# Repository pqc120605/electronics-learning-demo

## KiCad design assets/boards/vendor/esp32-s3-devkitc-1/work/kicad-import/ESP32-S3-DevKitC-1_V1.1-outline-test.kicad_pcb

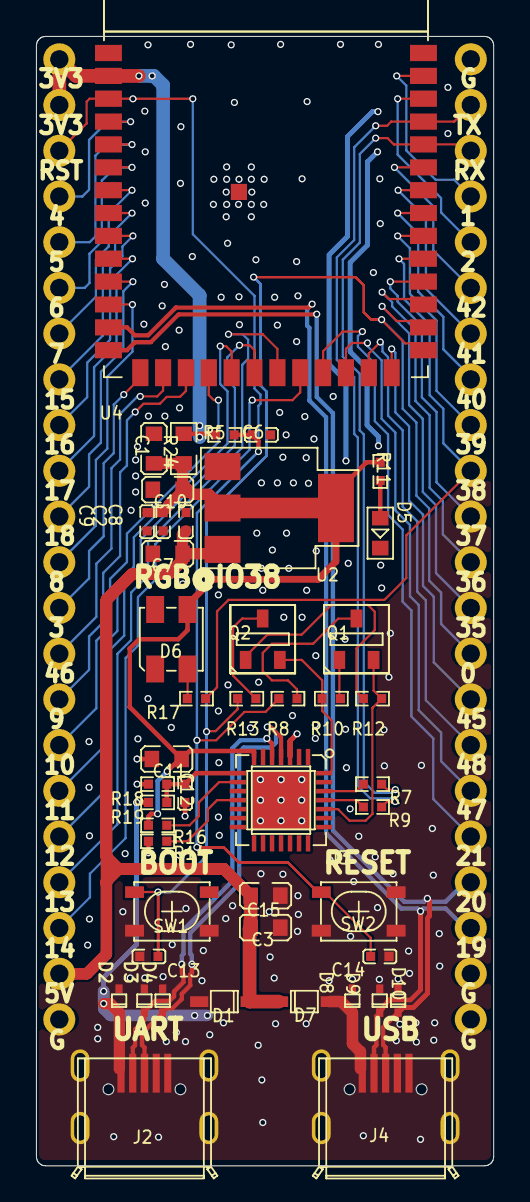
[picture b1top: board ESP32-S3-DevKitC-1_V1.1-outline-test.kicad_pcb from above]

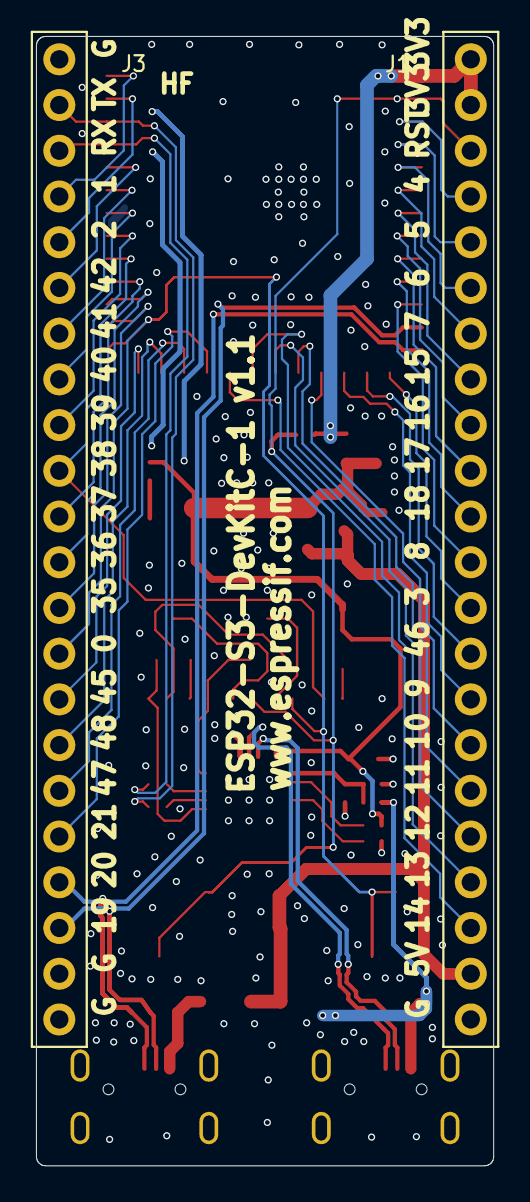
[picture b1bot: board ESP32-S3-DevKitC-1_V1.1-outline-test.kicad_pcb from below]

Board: 2 copper layers, 25.4 x 62.7 mm, 48 parts (2 on the bottom side), 58 nets.

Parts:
C1, C3, C7, C10, C11, C15: C0603
C2, C6, C8, C9, C12, C13, C14: C0402
D1, D7: SOD123
D2, D3, D4, D8, D9, D10: SOD523
D5: LED0603
D6: LED3535B
J1, J3: CON22X1_2P54_OBLATE
J2, J4: USB_5P_MICRO_F_ML
Q1, Q2: SOT23-3
R5, R7, R8, R9, R10, R11, R12, R13, R14, R16, R17, R18, R19: R0402
R24: R0603
SW1, SW2: SW4-4P2X3P2X2P5-SMT
U2: SOT223
U3: QFN28_0P5_5
U4: ESP32-S3-WROOM_NEW

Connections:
CHIP_PU: C6.1, C14.2, J1.3, R5.1, R8.2, SW2.3, U4.3
D+: D4.2, J2.3, U3.4
D-: D3.2, J2.2, U3.5
DTR: Q2.2, R10.1, U3.28
ESP_3V3: J1.1, J1.2, R5.2, R24.2, U4.2
GND: C1.2, C2.2, C3.2, C6.2, C7.2, C8.2, C9.2, C10.2, C11.2, C12.2, C13.1, C14.1, C15.2, D2.1, D3.1, D4.1, D5.2, D6.1, D8.1, D9.1, D10.1, J1.22, J2.5, J2.6, J2.7, J2.8, J2.9, J3.1, J3.21, J3.22, J4.5, J4.6, J4.7, J4.8, J4.9, R14.2, R18.2, SW1.1, SW2.1, U2.1, U3.3, U3.29, U4.1, U4.40, U4.41
GPIO0: C13.2, J3.14, R13.2, SW1.3, U4.27
GPIO1: J3.4, U4.39
GPIO2: J3.5, U4.38
GPIO3: J1.13, U4.15
GPIO4: J1.4, U4.4
GPIO5: J1.5, U4.5
GPIO6: J1.6, U4.6
GPIO7: J1.7, U4.7
GPIO8: J1.12, U4.12
GPIO9: J1.15, U4.17
GPIO10: J1.16, U4.18
GPIO11: J1.17, U4.19
GPIO12: J1.18, U4.20
GPIO13: J1.19, U4.21
GPIO14: J1.20, U4.22
GPIO15: J1.8, U4.8
GPIO16: J1.9, U4.9
GPIO17: J1.10, U4.10
GPIO18: J1.11, U4.11
GPIO19: D9.2, J3.20, J4.2, U4.13
GPIO20: D10.2, J3.19, J4.3, U4.14
GPIO21: J3.18, U4.23
GPIO35: J3.13, U4.28
GPIO36: J3.12, U4.29
GPIO37: J3.11, U4.30
GPIO38: J3.10, R17.1, U4.31
GPIO39: J3.9, U4.32
GPIO40: J3.8, U4.33
GPIO41: J3.7, U4.34
GPIO42: J3.6, U4.35
GPIO45: J3.15, U4.26
GPIO46: J1.14, U4.16
GPIO47: J3.17, U4.24
GPIO48: J3.16, U4.25
N17688270: C12.1, R18.1, R19.2, U3.8
N17688616: R16.1, U3.9
N17688663: R14.1, U3.11
N17689011: R7.1, U3.26
N17689016: R9.1, U3.25
N17689859: Q1.1, R10.2
N17689862: Q2.1, R12.2
N17689962: Q2.3, R13.1
N17689967: Q1.3, R8.1
N17692194: D5.1, R11.2
RGB_CTRL: D6.2, R17.2
RTS: Q1.2, R12.1, U3.24
U0RXD: J3.3, R7.2, U4.36
U0TXD: J3.2, R9.2, U4.37
VBUS: D1.1, D2.2, J2.1, R19.1
VBUSB: D7.1, D8.2, J4.1
VCC_3V3: C1.1, C2.1, C9.1, C10.1, C11.1, D6.3, R11.1, R16.2, R24.1, U2.2, U2.4, U3.6, U3.7
VCC_5V: C3.1, C7.1, C8.1, C15.1, D1.2, D7.2, J1.21, U2.3

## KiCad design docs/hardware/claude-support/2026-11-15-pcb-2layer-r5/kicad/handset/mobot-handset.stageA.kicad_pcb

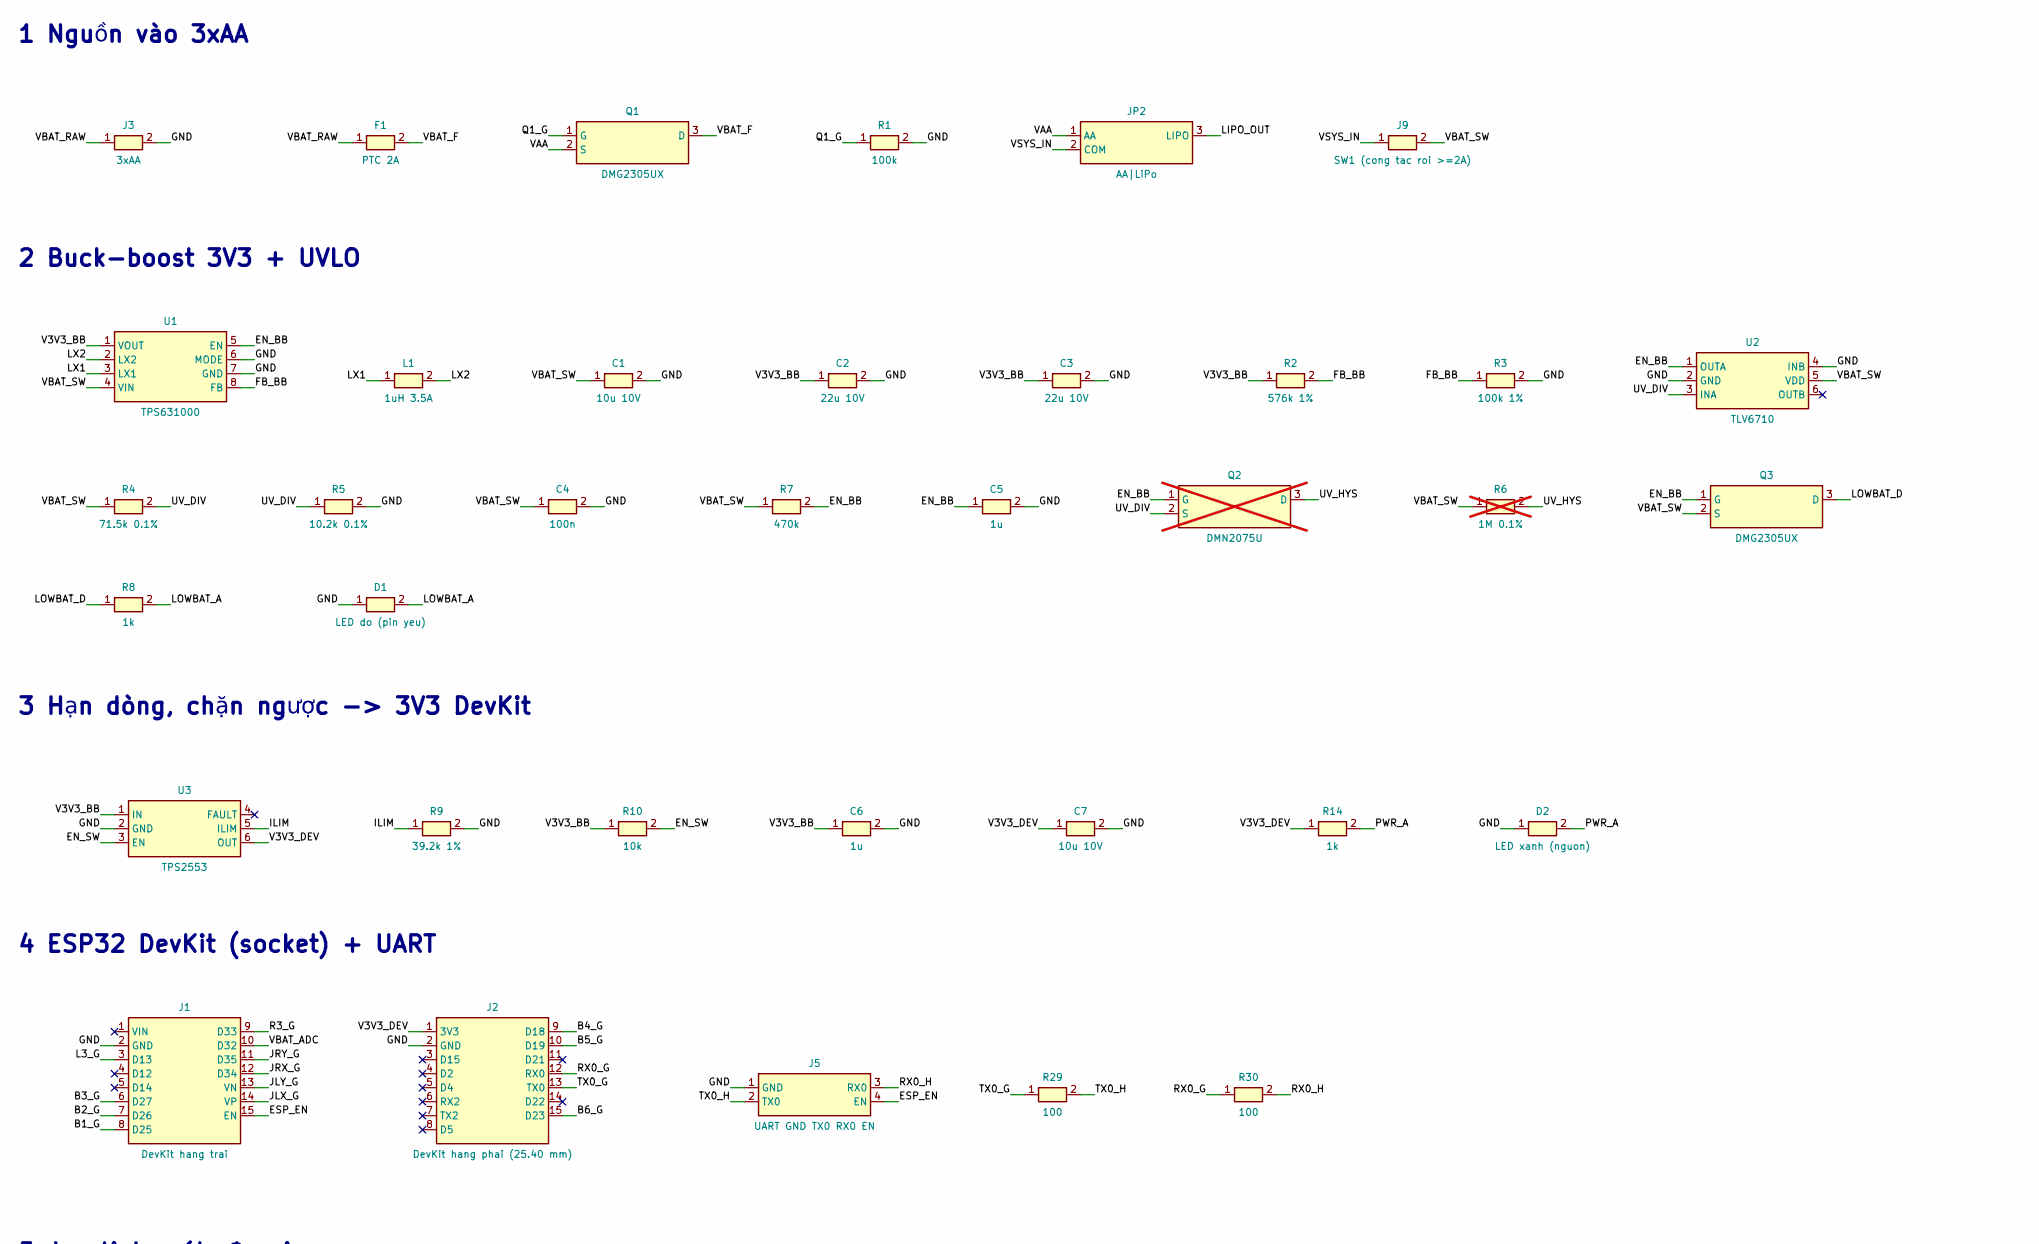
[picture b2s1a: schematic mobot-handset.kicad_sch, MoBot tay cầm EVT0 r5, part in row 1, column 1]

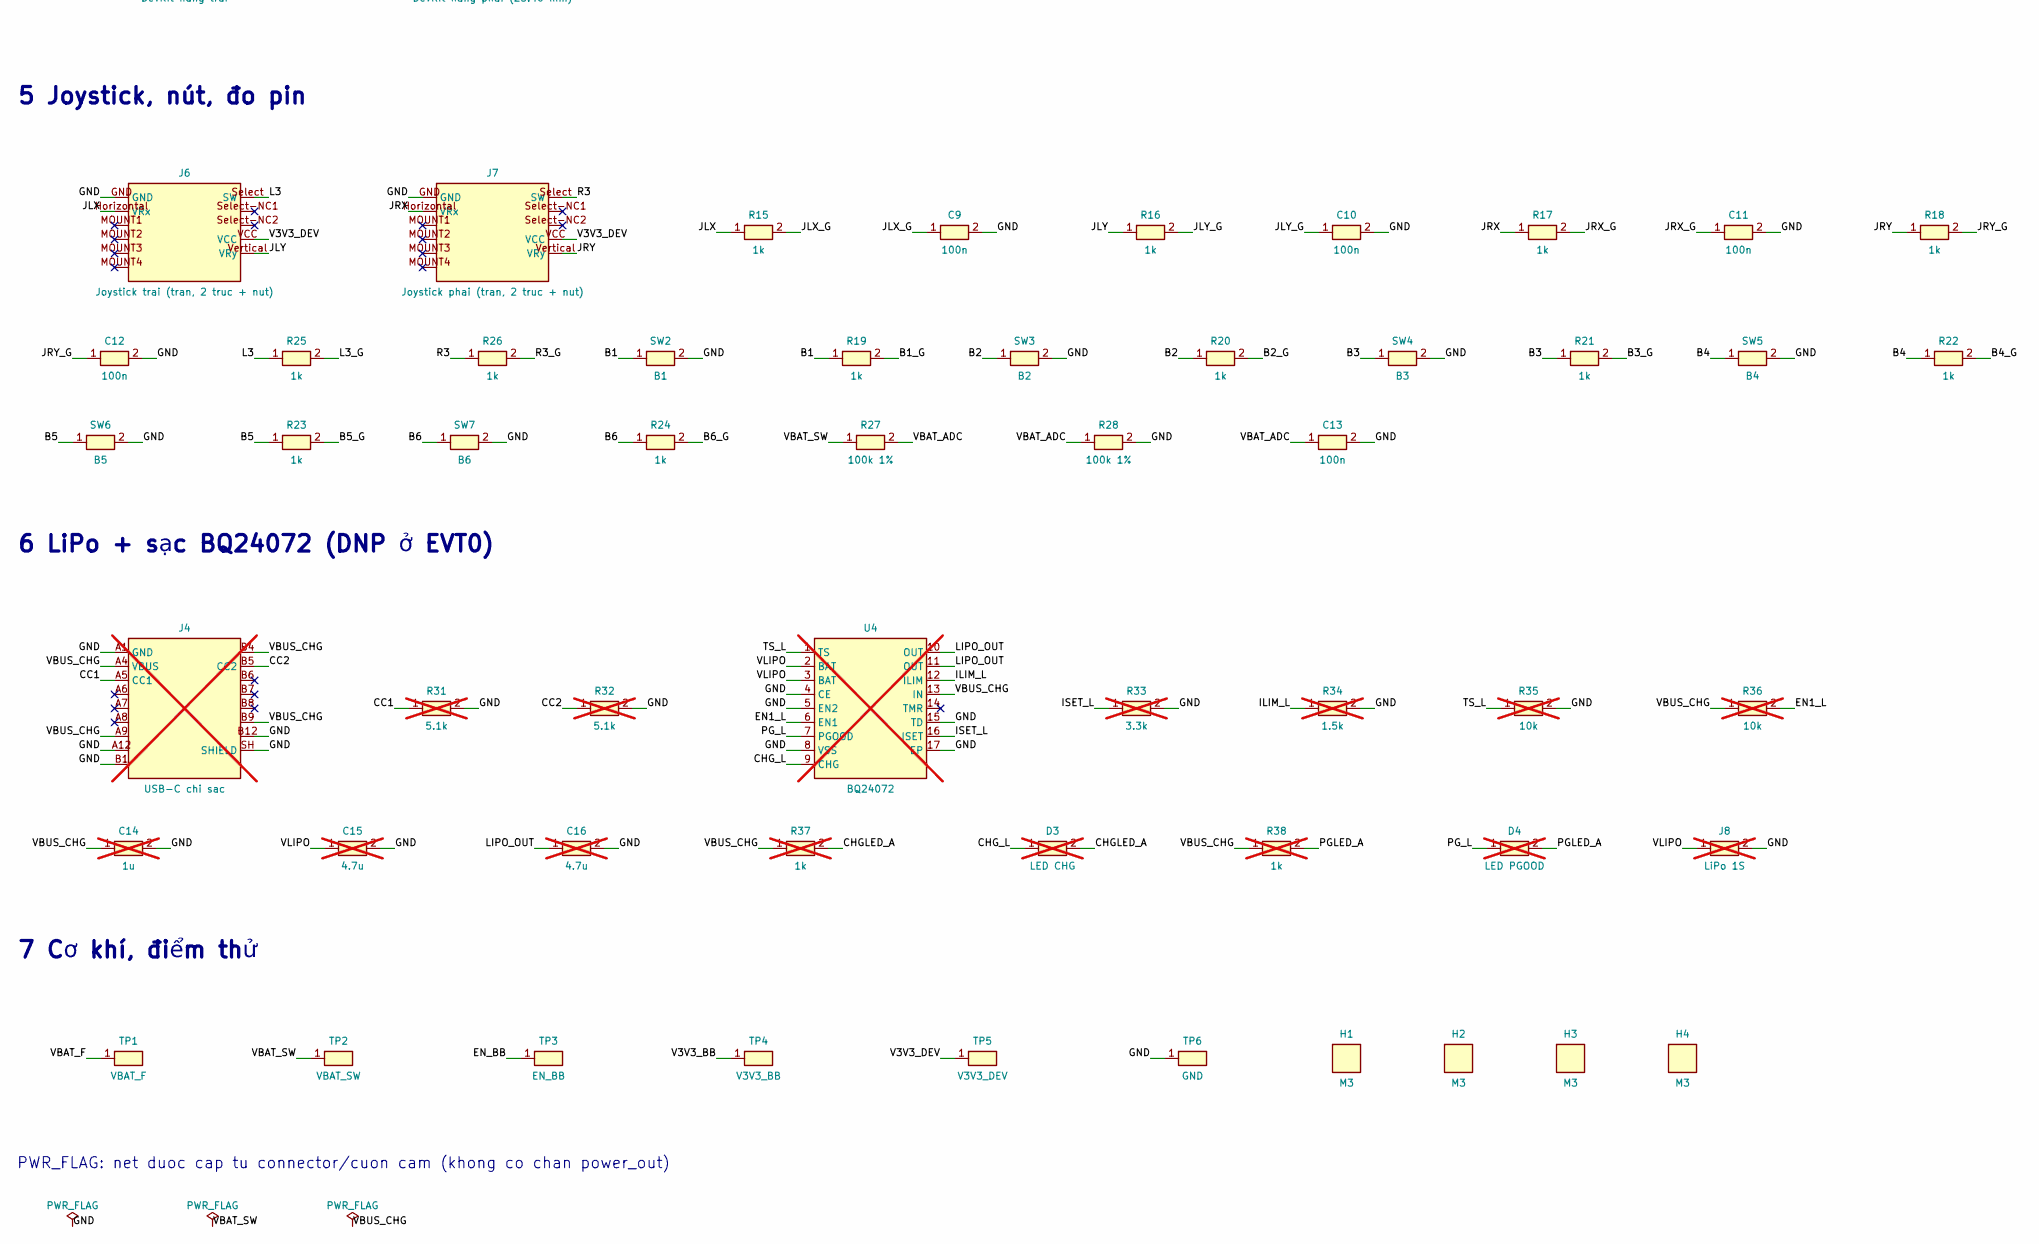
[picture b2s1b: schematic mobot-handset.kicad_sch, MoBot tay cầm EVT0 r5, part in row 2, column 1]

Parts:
C1, C7: 10u 10V; C_0805_2012Metric
C2, C3: 22u 10V; C_0805_2012Metric
C4, C9, C10, C11, C12, C13: 100n; C_0603_1608Metric
C5, C6: 1u; C_0603_1608Metric
C14: 1u; C_0603_1608Metric; not fitted
C15, C16: 4.7u; C_0603_1608Metric; not fitted
D1: LED do (pin yeu); LED_0603_1608Metric
D2: LED xanh (nguon); LED_0603_1608Metric
D3: LED CHG; LED_0603_1608Metric; not fitted
D4: LED PGOOD; LED_0603_1608Metric; not fitted
F1: PTC 2A; Fuse_1812_4532Metric; MPN MF-MSMF200/8X
H1, H2, H3, H4: M3; MountingHole_3.2mm_M3
J1: DevKit hang trai; PinSocket_1x15_P2.54mm_Vertical
J2: DevKit hang phai (25.40 mm); PinSocket_1x15_P2.54mm_Vertical
J3: 3xAA; JST_XH_B2B-XH-A_1x02_P2.50mm_Vertical; MPN B2B-XH-A
J4: USB-C chi sac; USB_C_Receptacle_GCT_USB4105-xx-A_16P_TopMnt_Horizontal; MPN USB4105-GF-A; not fitted
J5: UART GND TX0 RX0 EN; PinHeader_1x04_P2.54mm_Vertical
J6: Joystick trai (tran, 2 truc + nut); Joystick_PTH
J7: Joystick phai (tran, 2 truc + nut); Joystick_PTH
J8: LiPo 1S; JST_PH_B2B-PH-K_1x02_P2.00mm_Vertical; MPN B2B-PH-K-S; not fitted
J9: SW1 (cong tac roi >=2A); JST_XH_B2B-XH-A_1x02_P2.50mm_Vertical; MPN B2B-XH-A
JP2: AA|LiPo; SolderJumper-3_P1.3mm_Bridged12_RoundedPad1.0x1.5mm
L1: 1uH 3.5A; L_Changjiang_FNR4030S; MPN XEL4030-102ME
Q1, Q3: DMG2305UX; SOT-23; MPN DMG2305UX-7
Q2: DMN2075U; SOT-23; MPN DMN2075U-7; not fitted
R1: 100k; R_0603_1608Metric
R2: 576k 1%; R_0603_1608Metric
R3, R27, R28: 100k 1%; R_0603_1608Metric
R4: 71.5k 0.1%; R_0603_1608Metric
R5: 10.2k 0.1%; R_0603_1608Metric
R6: 1M 0.1%; R_0603_1608Metric; not fitted
R7: 470k; R_0603_1608Metric
R8, R14, R15, R16, R17, R18, R19, R20, R21, R22, R23, R24, R25, R26: 1k; R_0603_1608Metric
R9: 39.2k 1%; R_0603_1608Metric
R10: 10k; R_0603_1608Metric
R29, R30: 100; R_0603_1608Metric
R31, R32: 5.1k; R_0603_1608Metric; not fitted
R33: 3.3k; R_0603_1608Metric; not fitted
R34: 1.5k; R_0603_1608Metric; not fitted
R35, R36: 10k; R_0603_1608Metric; not fitted
R37, R38: 1k; R_0603_1608Metric; not fitted
SW2: B1; SW_PUSH_6mm
SW3: B2; SW_PUSH_6mm
SW4: B3; SW_PUSH_6mm
SW5: B4; SW_PUSH_6mm
SW6: B5; SW_PUSH_6mm
SW7: B6; SW_PUSH_6mm
TP1: VBAT_F; TestPoint_Pad_D1.5mm
TP2: VBAT_SW; TestPoint_Pad_D1.5mm
TP3: EN_BB; TestPoint_Pad_D1.5mm
TP4: V3V3_BB; TestPoint_Pad_D1.5mm
TP5: V3V3_DEV; TestPoint_Pad_D1.5mm
TP6: GND; TestPoint_Pad_D1.5mm
U1: TPS631000; SOT-583-8; MPN TPS631000DRLR
U2: TLV6710; TSOT-23-6; MPN TLV6710DDCR
U3: TPS2553; SOT-23-6; MPN TPS2553DBVR
U4: BQ24072; VQFN-16-1EP_3x3mm_P0.5mm_EP1.68x1.68mm; MPN BQ24072RGTR; not fitted

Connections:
/B1: R19.1, SW2.1
/B1_G: J1.8 (D25), R19.2
/B2: R20.1, SW3.1
/B2_G: J1.7 (D26), R20.2
/B3: R21.1, SW4.1
/B3_G: J1.6 (D27), R21.2
/B4: R22.1, SW5.1
/B4_G: J2.9 (D18), R22.2
/B5: R23.1, SW6.1
/B5_G: J2.10 (D19), R23.2
/B6: R24.1, SW7.1
/B6_G: J2.15 (D23), R24.2
/CC1: J4.A5 (CC1), R31.1
/CC2: J4.B5 (CC2), R32.1
/CHGLED_A: D3.2 (A), R37.2
/CHG_L: D3.1 (K), U4.9 (CHG)
/EN1_L: R36.2, U4.6 (EN1)
/EN_BB: C5.1, Q2.1 (G), Q3.1 (G), R7.2, TP3.1, U1.5 (EN), U2.1 (OUTA)
/EN_SW: R10.2, U3.3 (EN)
/ESP_EN: J1.15 (EN), J5.4 (EN)
/FB_BB: R2.2, R3.1, U1.8 (FB)
/GND: C1.2, C2.2, C3.2, C4.2, C5.2, C6.2, C7.2, C9.2, C10.2, C11.2, C12.2, C13.2, C14.2, C15.2, C16.2, D1.1 (K), D2.1 (K), J1.2 (GND), J2.2 (GND), J3.2 (-), J4.A1 (GND), J4.A12, J4.B1, J4.B12, J4.SH (SHIELD), J5.1 (GND), J6.GND, J7.GND, J8.2 (-), R1.2, R3.2, R5.2, R9.2, R28.2, R31.2, R32.2, R33.2, R34.2, R35.2, SW2.2, SW3.2, SW4.2, SW5.2, SW6.2, SW7.2, TP6.1, U1.6 (MODE), U1.7 (GND), U2.2 (GND), U2.4 (INB), U3.2 (GND), U4.4 (CE), U4.5 (EN2), U4.8 (VSS), U4.15 (TD), U4.17 (EP)
/ILIM: R9.1, U3.5 (ILIM)
/ILIM_L: R34.1, U4.12 (ILIM)
/ISET_L: R33.1, U4.16 (ISET)
/JLX: J6.Horizontal (VRx), R15.1
/JLX_G: C9.1, J1.14 (VP), R15.2
/JLY: J6.Vertical (VRy), R16.1
/JLY_G: C10.1, J1.13 (VN), R16.2
/JRX: J7.Horizontal (VRx), R17.1
/JRX_G: C11.1, J1.12 (D34), R17.2
/JRY: J7.Vertical (VRy), R18.1
/JRY_G: C12.1, J1.11 (D35), R18.2
/L3: J6.Select (SW), R25.1
/L3_G: J1.3 (D13), R25.2
/LIPO_OUT: C16.1, JP2.3 (LIPO), U4.10 (OUT), U4.11 (OUT)
/LOWBAT_A: D1.2 (A), R8.2
/LOWBAT_D: Q3.3 (D), R8.1
/LX1: L1.1, U1.3 (LX1)
/LX2: L1.2, U1.2 (LX2)
/PGLED_A: D4.2 (A), R38.2
/PG_L: D4.1 (K), U4.7 (PGOOD)
/PWR_A: D2.2 (A), R14.2
/Q1_G: Q1.1 (G), R1.1
/R3: J7.Select (SW), R26.1
/R3_G: J1.9 (D33), R26.2
/RX0_G: J2.12 (RX0), R30.1
/RX0_H: J5.3 (RX0), R30.2
/TS_L: R35.1, U4.1 (TS)
/TX0_G: J2.13 (TX0), R29.1
/TX0_H: J5.2 (TX0), R29.2
/UV_DIV: Q2.2 (S), R4.2, R5.1, U2.3 (INA)
/UV_HYS: Q2.3 (D), R6.2
/V3V3_BB: C2.1, C3.1, C6.1, R2.1, R10.1, TP4.1, U1.1 (VOUT), U3.1 (IN)
/V3V3_DEV: C7.1, J2.1 (3V3), J6.VCC, J7.VCC, R14.1, TP5.1, U3.6 (OUT)
/VAA: JP2.1 (AA), Q1.2 (S)
/VBAT_ADC: C13.1, J1.10 (D32), R27.2, R28.1
/VBAT_F: F1.2, Q1.3 (D), TP1.1
/VBAT_RAW: F1.1, J3.1 (+)
/VBAT_SW: C1.1, C4.1, J9.2 (OUT), Q3.2 (S), R4.1, R6.1, R7.1, R27.1, TP2.1, U1.4 (VIN), U2.5 (VDD)
/VBUS_CHG: C14.1, J4.A4 (VBUS), J4.A9, J4.B4, J4.B9, R36.1, R37.1, R38.1, U4.13 (IN)
/VLIPO: C15.1, J8.1 (+), U4.2 (BAT), U4.3 (BAT)
/VSYS_IN: J9.1 (IN), JP2.2 (COM)

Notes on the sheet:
1 Nguồn vào 3xAA
2 Buck-boost 3V3 + UVLO
3 Hạn dòng, chặn ngược -> 3V3 DevKit
4 ESP32 DevKit (socket) + UART
5 Joystick, nút, đo pin
6 LiPo + sạc BQ24072 (DNP ở EVT0)
7 Cơ khí, điểm thử
PWR_FLAG: net duoc cap tu connector/cuon cam (khong co chan power_out)

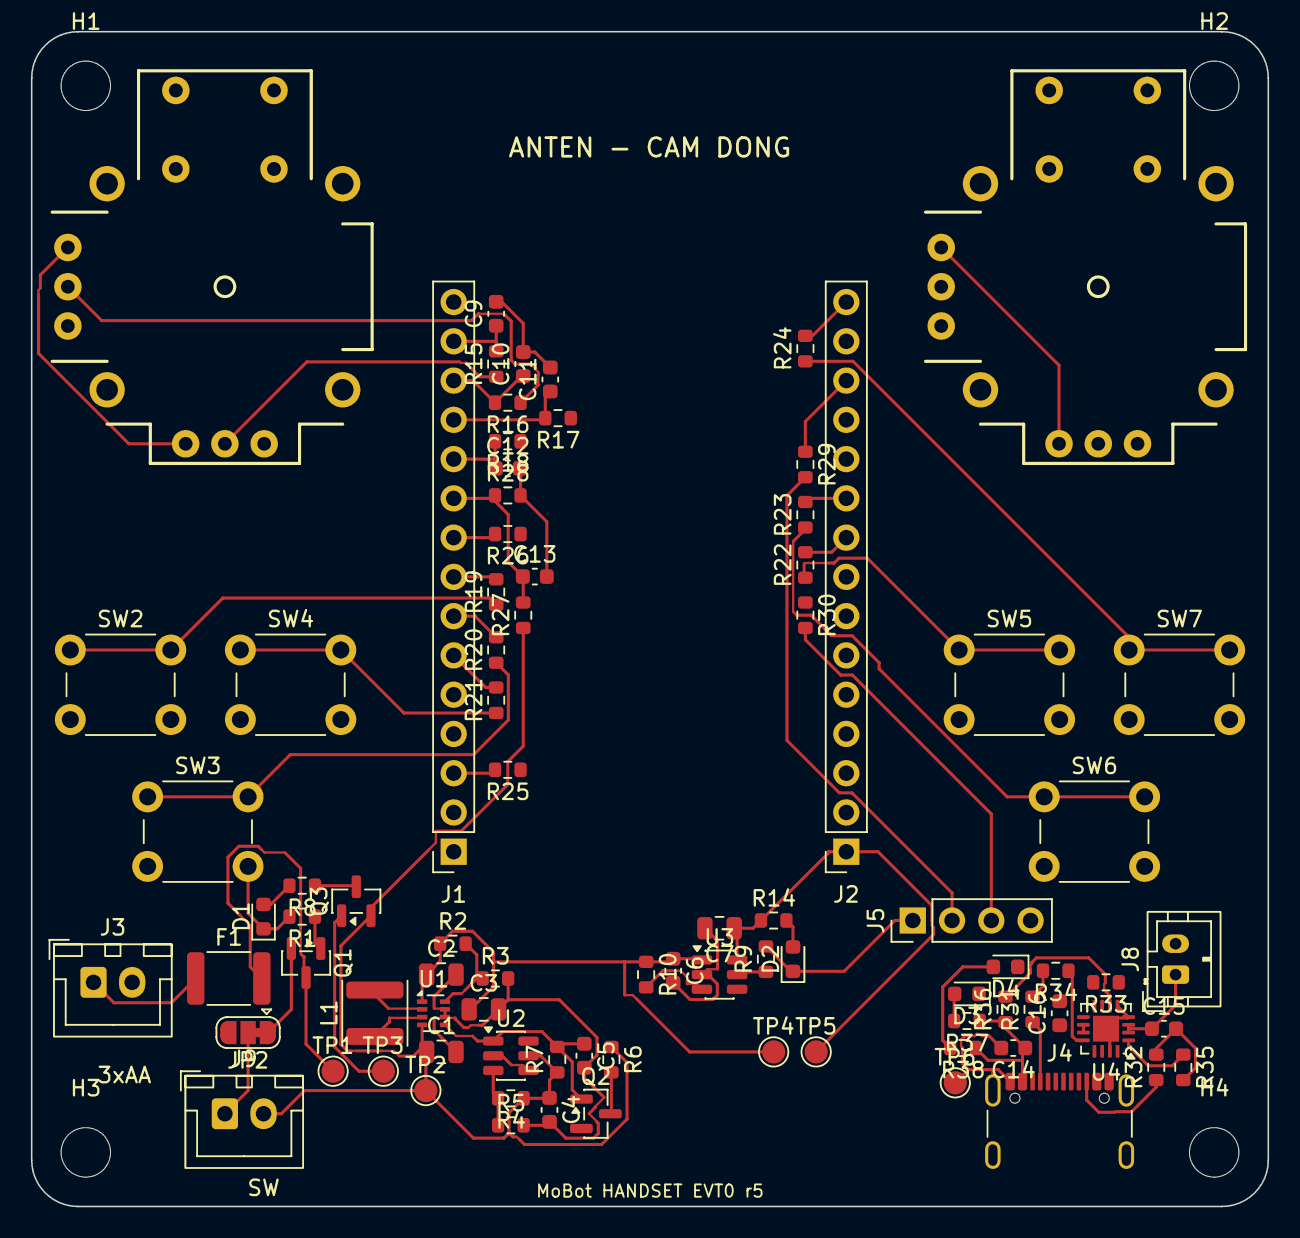
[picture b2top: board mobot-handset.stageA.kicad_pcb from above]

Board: 2 copper layers, 80.0 x 76.0 mm, 89 parts (0 on the bottom side), 63 nets.

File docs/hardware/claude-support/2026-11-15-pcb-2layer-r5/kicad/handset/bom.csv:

"Reference","Value","Footprint","MPN","QUANTITY","DNP"
"C1,C7","10u 10V","Capacitor_SMD:C_0805_2012Metric","","2",""
"C2,C3","22u 10V","Capacitor_SMD:C_0805_2012Metric","","2",""
"C4,C9-C13","100n","Capacitor_SMD:C_0603_1608Metric","","6",""
"C5,C6","1u","Capacitor_SMD:C_0603_1608Metric","","2",""
"C14","1u","Capacitor_SMD:C_0603_1608Metric","","1","DNP"
"C15,C16","4.7u","Capacitor_SMD:C_0603_1608Metric","","2","DNP"
"D1","LED do (pin yeu)","LED_SMD:LED_0603_1608Metric","","1",""
"D2","LED xanh (nguon)","LED_SMD:LED_0603_1608Metric","","1",""
"D3","LED CHG","LED_SMD:LED_0603_1608Metric","","1","DNP"
"D4","LED PGOOD","LED_SMD:LED_0603_1608Metric","","1","DNP"
"F1","PTC 2A","Fuse:Fuse_1812_4532Metric","MF-MSMF200/8X","1",""
"J1","DevKit hang trai","Connector_PinSocket_2.54mm:PinSocket_1x15_P2.54mm_Vertical","","1",""
"J2","DevKit hang phai (25.40 mm)","Connector_PinSocket_2.54mm:PinSocket_1x15_P2.54mm_Vertical","","1",""
"J3","3xAA","Connector_JST:JST_XH_B2B-XH-A_1x02_P2.50mm_Vertical","B2B-XH-A","1",""
"J4","USB-C chi sac","Connector_USB:USB_C_Receptacle_GCT_USB4105-xx-A_16P_TopMnt_Horizontal","USB4105-GF-A","1","DNP"
"J5","UART GND TX0 RX0 EN","Connector_PinHeader_2.54mm:PinHeader_1x04_P2.54mm_Vertical","","1",""
"J6","Joystick trai (tran, 2 truc + nut)","mobot:Joystick_PTH","","1",""
"J7","Joystick phai (tran, 2 truc + nut)","mobot:Joystick_PTH","","1",""
"J8","LiPo 1S","Connector_JST:JST_PH_B2B-PH-K_1x02_P2.00mm_Vertical","B2B-PH-K-S","1","DNP"
"J9","SW1 (cong tac roi >=2A)","Connector_JST:JST_XH_B2B-XH-A_1x02_P2.50mm_Vertical","B2B-XH-A","1",""
"L1","1uH 3.5A","Inductor_SMD:L_Changjiang_FNR4030S","XEL4030-102ME","1",""
"Q1,Q3","DMG2305UX","Package_TO_SOT_SMD:SOT-23","DMG2305UX-7","2",""
"Q2","DMN2075U","Package_TO_SOT_SMD:SOT-23","DMN2075U-7","1","DNP"
"R1","100k","Resistor_SMD:R_0603_1608Metric","","1",""
"R2","576k 1%","Resistor_SMD:R_0603_1608Metric","","1",""
"R3,R27,R28","100k 1%","Resistor_SMD:R_0603_1608Metric","","3",""
"R4","71.5k 0.1%","Resistor_SMD:R_0603_1608Metric","","1",""
"R5","10.2k 0.1%","Resistor_SMD:R_0603_1608Metric","","1",""
"R6","1M 0.1%","Resistor_SMD:R_0603_1608Metric","","1","DNP"
"R7","470k","Resistor_SMD:R_0603_1608Metric","","1",""
"R8,R14-R26","1k","Resistor_SMD:R_0603_1608Metric","","14",""
"R9","39.2k 1%","Resistor_SMD:R_0603_1608Metric","","1",""
"R10","10k","Resistor_SMD:R_0603_1608Metric","","1",""
"R29,R30","100","Resistor_SMD:R_0603_1608Metric","","2",""
"R31,R32","5.1k","Resistor_SMD:R_0603_1608Metric","","2","DNP"
"R33","3.3k","Resistor_SMD:R_0603_1608Metric","","1","DNP"
"R34","1.5k","Resistor_SMD:R_0603_1608Metric","","1","DNP"
"R35,R36","10k","Resistor_SMD:R_0603_1608Metric","","2","DNP"
"R37,R38","1k","Resistor_SMD:R_0603_1608Metric","","2","DNP"
"SW2","B1","Button_Switch_THT:SW_PUSH_6mm","","1",""
"SW3","B2","Button_Switch_THT:SW_PUSH_6mm","","1",""
"SW4","B3","Button_Switch_THT:SW_PUSH_6mm","","1",""
"SW5","B4","Button_Switch_THT:SW_PUSH_6mm","","1",""
"SW6","B5","Button_Switch_THT:SW_PUSH_6mm","","1",""
"SW7","B6","Button_Switch_THT:SW_PUSH_6mm","","1",""
"U1","TPS631000","Package_TO_SOT_SMD:SOT-583-8","TPS631000DRLR","1",""
"U2","TLV6710","Package_TO_SOT_SMD:TSOT-23-6","TLV6710DDCR","1",""
"U3","TPS2553","Package_TO_SOT_SMD:SOT-23-6","TPS2553DBVR","1",""
"U4","BQ24072","Package_DFN_QFN:VQFN-16-1EP_3x3mm_P0.5mm_EP1.68x1.68mm","BQ24072RGTR","1","DNP"
